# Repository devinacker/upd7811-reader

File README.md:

This is a PCB designed to read the internal mask ROM contents from NEC "µCOM-87AD" microcontrollers (µPD7811 aka uPD7811, etc.) and automatically output them in Intel hex format over serial.

# Specs

- Support for all NEC "µCOM-87AD" series microcontrollers:
  - uPD7811
  - uPD78C11
  - uPD78C12
  - uPD78C14
  - uPD78C18
- Automatic ROM size detection (4/8/16/32kb)
- Power input: 7.5-9V DC, center positive
- Serial output: 115200 baud, 8N1, Intel hex format

# Usage

Zipped gerbers and ROM are available from the releases page.

- Burn the firmware ROM to a 27C256 or compatible EPROM or flash chip (e.g. Atmel AT29C256, Winbond W27E257).
- Assemble the board (all parts are through-hole for convenience).
- Connect the 2-pin serial header to a USB UART adapter or something similar. Configure your computer's serial port as described in "Specs".
- Plug in power and turn the board on. The ROM dump will automatically start being dumped over serial. The "Ready" LED will flash while this is in progress, then becomes solid once it's finished.
- Press Reset or cycle power to dump again, if needed.

The resulting Intel hex file can be converted to a raw ROM image using objcopy, SRecord, or similar tools.

# Parts

| Ref | Part |
| --- | --- |
| C1, C2 | 22pF ceramic |
| C3, C4, C5, C6, C7, C8 | 0.1µF ceramic |
| C9 | 0.22µF electrolytic |
| D1 | generic 5mm 2V LED (power) |
| D2 | generic 5mm 2V LED (status) |
| D3 | 1N4001 |
| J1 | generic 3-pin barrel jack |
| J2 | 1x2 pin header, 2.54mm |
| R1, R2 | 22k ohm, 1/8 watt |
| R3, R4, R5, R6, R7 | 1k ohm, 1/8 watt |
| RN1, RN2, RN5, RN6 | 9-pin 22k ohm SIP resistors |
| RN3, RN4 | 5-pin 22k ohm SIP resistors |
| SW1 | generic 6mm tactile switch (optional, for reset) |
| SW2 | OS102011MS2QN1 |
| U1 | µPD78(C)11/12/14/18, 64-pin QUIP<br/>(four 1x16 2.54mm machined pin sockets recommended)
| U2 | 74HCT373 |
| U3 | 74HCT14 |
| U4 | 27C256 EPROM or compatible |
| U5 | LM7805 |
| Y1 | 11.0592MHz crystal |

# Disclaimer

Use this board at your own risk. It was designed to be simple, but assumes you have basic experience working with electronics, including soldering. I am not responsible if you happen to blow something up.

# License

PCB design and schematics are released under the Creative Commons Attribution-ShareAlike 4.0 (CC BY-SA) license. The firmware source (in the `rom` directory) is released as public domain.

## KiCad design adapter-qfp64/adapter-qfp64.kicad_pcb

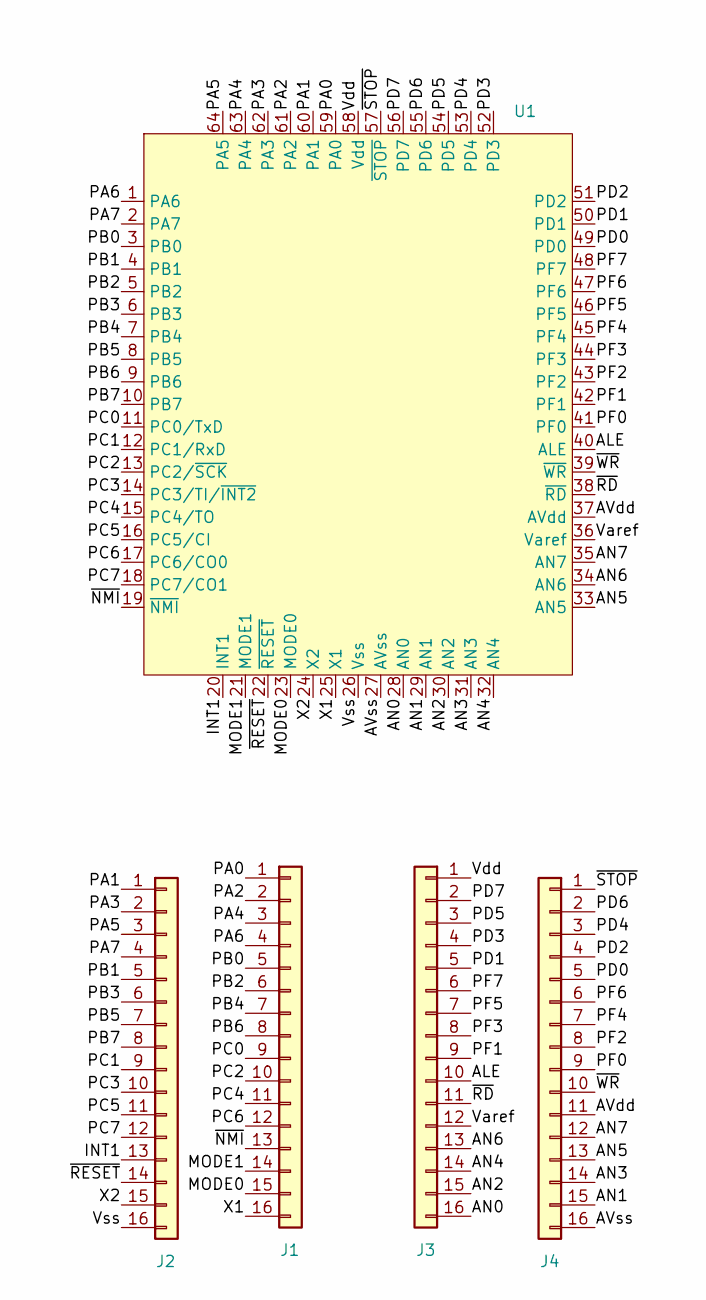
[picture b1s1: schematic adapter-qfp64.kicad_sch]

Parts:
J1, J2, J3, J4: Conn_01x16; PinHeader_1x16_P2.54mm_Vertical
U1: Package_QFP64

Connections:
/ALE: J3.10, U1.40 (ALE)
/AN0: J3.16, U1.28 (AN0)
/AN1: J4.15, U1.29 (AN1)
/AN2: J3.15, U1.30 (AN2)
/AN3: J4.14, U1.31 (AN3)
/AN4: J3.14, U1.32 (AN4)
/AN5: J4.13, U1.33 (AN5)
/AN6: J3.13, U1.34 (AN6)
/AN7: J4.12, U1.35 (AN7)
/AVdd: J4.11, U1.37 (AVdd)
/AVss: J4.16, U1.27 (AVss)
/INT1: J2.13, U1.20 (INT1)
/MODE0: J1.15, U1.23 (MODE0)
/MODE1: J1.14, U1.21 (MODE1)
/PA0: J1.1, U1.59 (PA0)
/PA1: J2.1, U1.60 (PA1)
/PA2: J1.2, U1.61 (PA2)
/PA3: J2.2, U1.62 (PA3)
/PA4: J1.3, U1.63 (PA4)
/PA5: J2.3, U1.64 (PA5)
/PA6: J1.4, U1.1 (PA6)
/PA7: J2.4, U1.2 (PA7)
/PB0: J1.5, U1.3 (PB0)
/PB1: J2.5, U1.4 (PB1)
/PB2: J1.6, U1.5 (PB2)
/PB3: J2.6, U1.6 (PB3)
/PB4: J1.7, U1.7 (PB4)
/PB5: J2.7, U1.8 (PB5)
/PB6: J1.8, U1.9 (PB6)
/PB7: J2.8, U1.10 (PB7)
/PC0: J1.9, U1.11 (PC0/TxD)
/PC1: J2.9, U1.12 (PC1/RxD)
/PC2: J1.10, U1.13 (PC2/~SCK)
/PC3: J2.10, U1.14 (PC3/TI/~INT2)
/PC4: J1.11, U1.15 (PC4/TO)
/PC5: J2.11, U1.16 (PC5/CI)
/PC6: J1.12, U1.17 (PC6/CO0)
/PC7: J2.12, U1.18 (PC7/CO1)
/PD0: J4.5, U1.49 (PD0)
/PD1: J3.5, U1.50 (PD1)
/PD2: J4.4, U1.51 (PD2)
/PD3: J3.4, U1.52 (PD3)
/PD4: J4.3, U1.53 (PD4)
/PD5: J3.3, U1.54 (PD5)
/PD6: J4.2, U1.55 (PD6)
/PD7: J3.2, U1.56 (PD7)
/PF0: J4.9, U1.41 (PF0)
/PF1: J3.9, U1.42 (PF1)
/PF2: J4.8, U1.43 (PF2)
/PF3: J3.8, U1.44 (PF3)
/PF4: J4.7, U1.45 (PF4)
/PF5: J3.7, U1.46 (PF5)
/PF6: J4.6, U1.47 (PF6)
/PF7: J3.6, U1.48 (PF7)
/Varef: J3.12, U1.36 (Varef)
/Vdd: J3.1, U1.58 (Vdd)
/Vss: J2.16, U1.26 (Vss)
/X1: J1.16, U1.25 (X1)
/X2: J2.15, U1.24 (X2)
/~NMI: J1.13, U1.19 (~NMI)
/~RD: J3.11, U1.38 (~RD)
/~RESET: J2.14, U1.22 (~RESET)
/~STOP: J4.1, U1.57 (~STOP)
/~WR: J4.10, U1.39 (~WR)

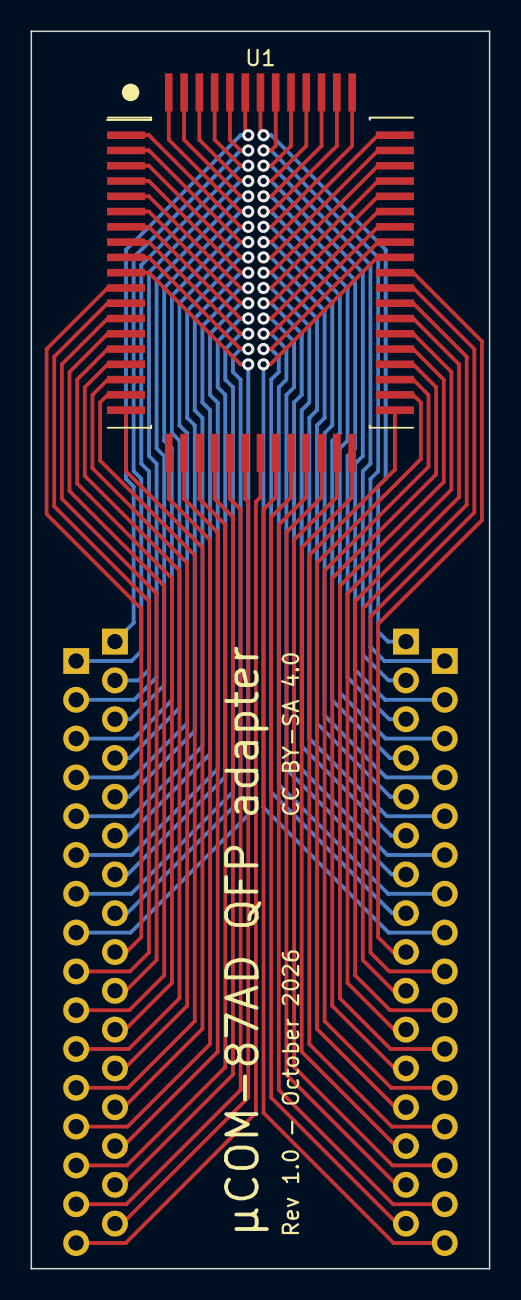
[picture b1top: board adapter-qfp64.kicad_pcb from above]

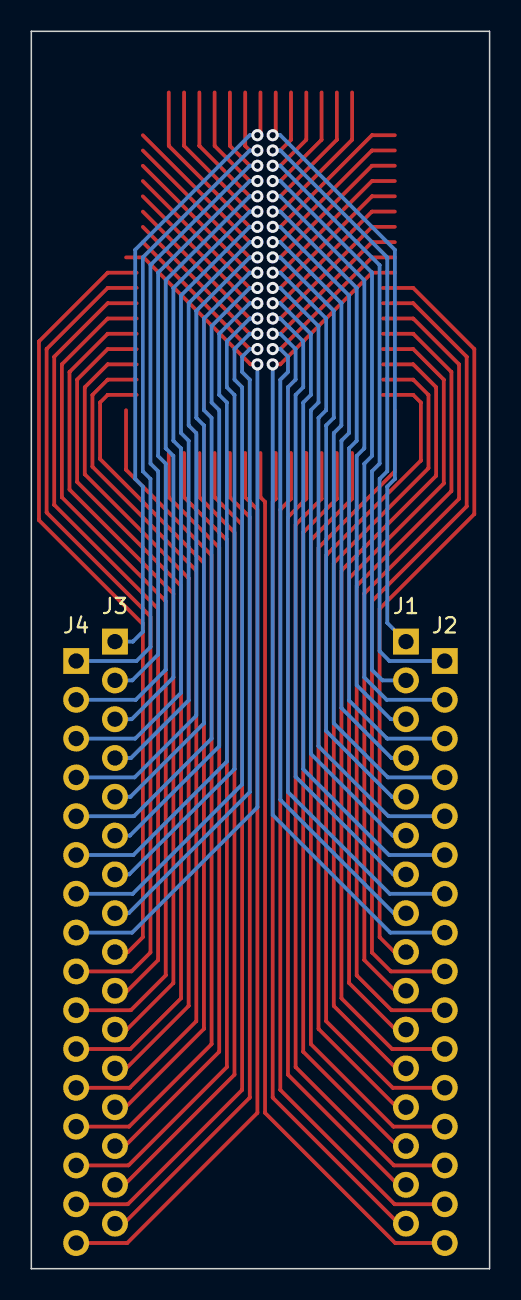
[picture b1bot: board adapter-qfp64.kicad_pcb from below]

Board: 2 copper layers, 30.0 x 81.0 mm, 5 parts (4 on the bottom side), 64 nets.

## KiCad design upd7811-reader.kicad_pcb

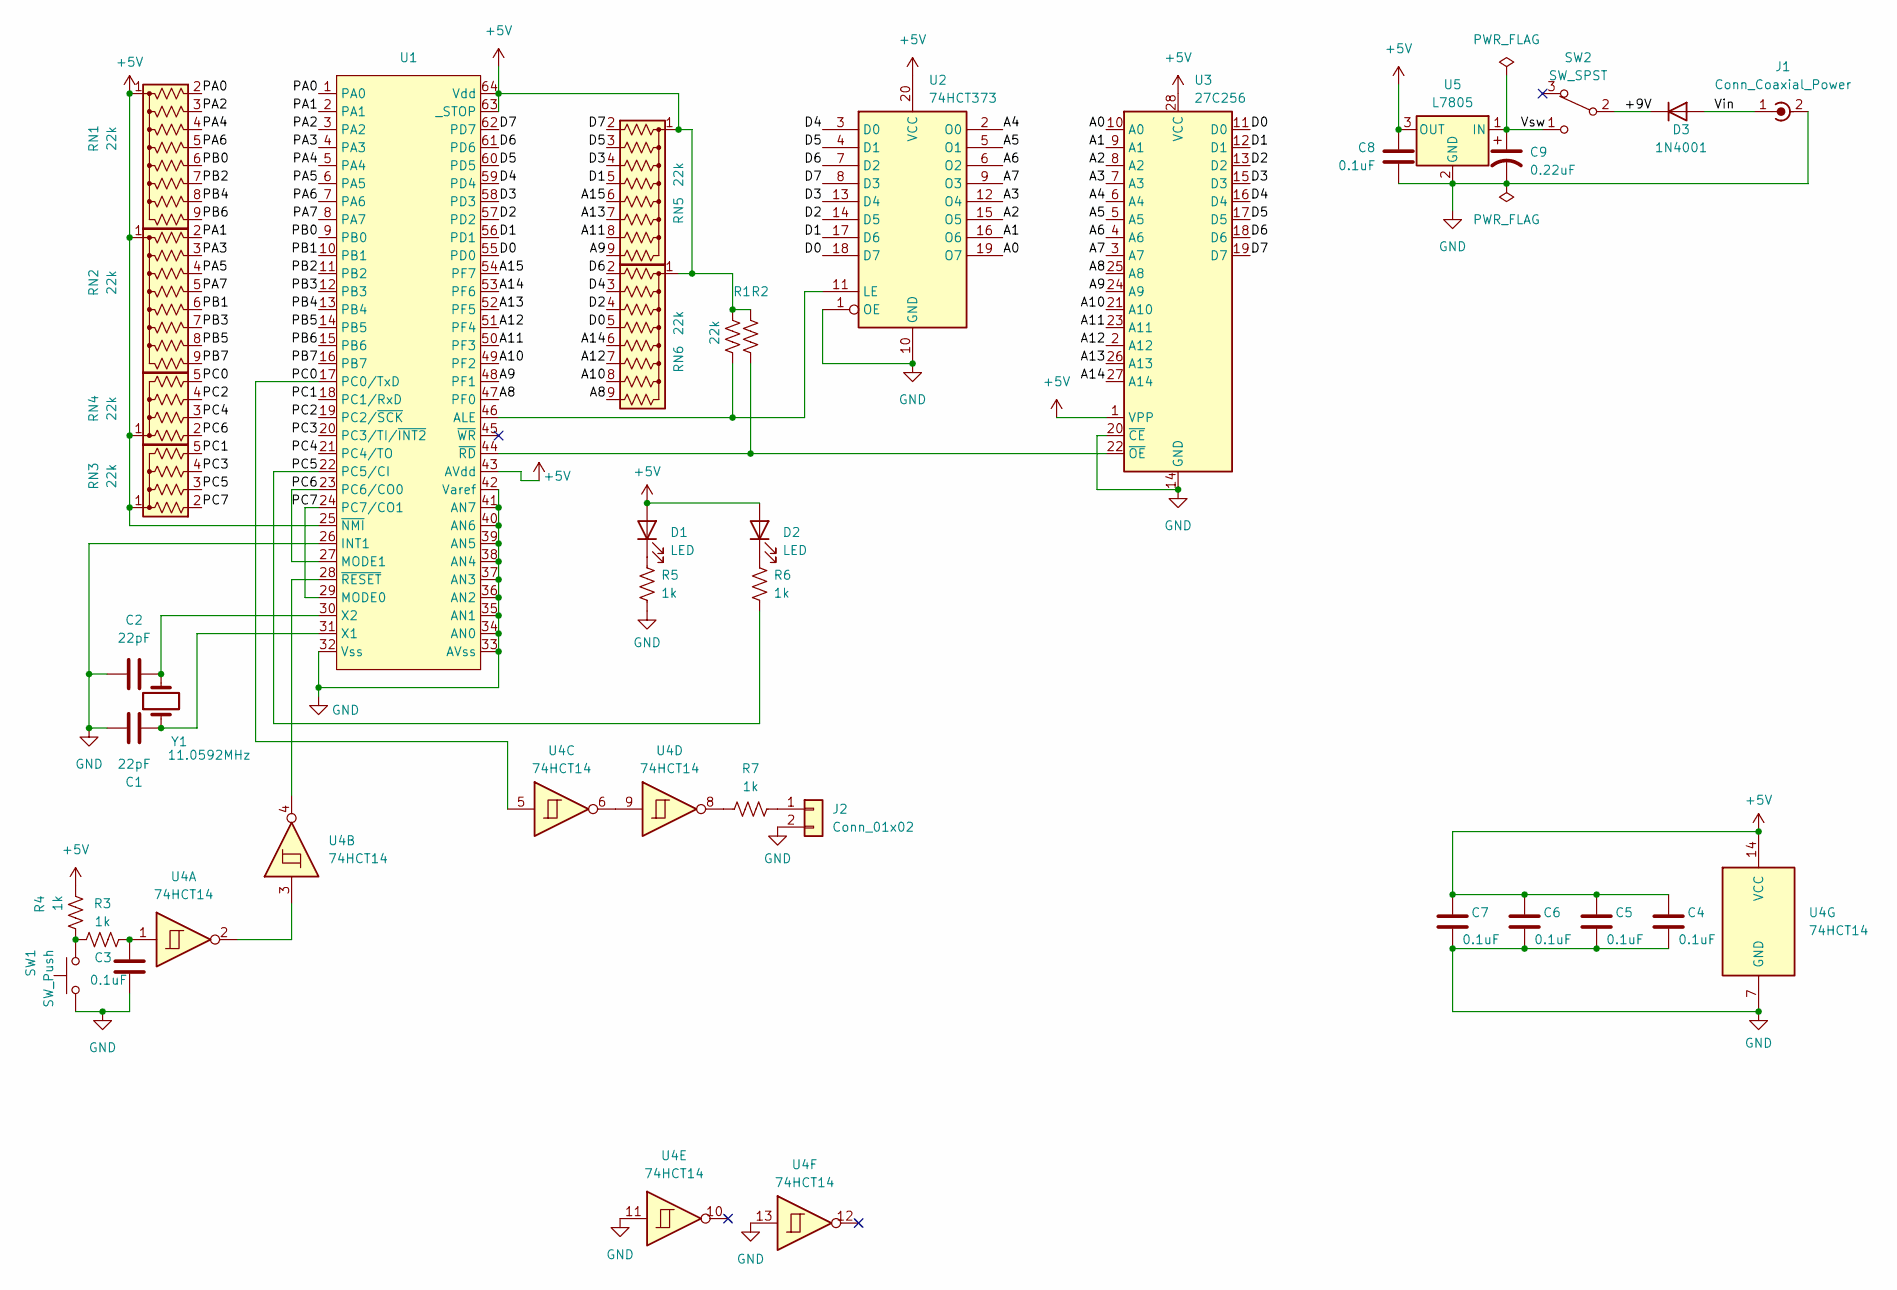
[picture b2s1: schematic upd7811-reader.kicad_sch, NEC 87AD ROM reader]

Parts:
C1, C2: 22pF; C_Disc_D3.8mm_W2.6mm_P2.50mm
C3, C4, C5, C6, C7, C8: 0.1uF; C_Disc_D3.8mm_W2.6mm_P2.50mm
C9: 0.22uF; CP_Radial_D5.0mm_P2.50mm
D1, D2: LED; LED_D5.0mm
D3: 1N4001; D_DO-41_SOD81_P10.16mm_Horizontal
J1: Conn_Coaxial_Power; BarrelJack_Wuerth_6941xx301002
J2: Conn_01x02; PinHeader_1x02_P2.54mm_Vertical
R1, R2: 22k; R_Axial_DIN0204_L3.6mm_D1.6mm_P5.08mm_Horizontal
R3, R4, R5, R6, R7: 1k; R_Axial_DIN0204_L3.6mm_D1.6mm_P5.08mm_Horizontal
RN1, RN2, RN5, RN6: 22k; R_Array_SIP9
RN3, RN4: 22k; R_Array_SIP5
SW1: SW_Push; SW_PUSH_6mm
SW2: SW_SPST; SW_Slide_1P2T_CK_OS102011MS2Q
U1: Package_QUIP64
U2: 74HCT373; DIP-20_W7.62mm
U3: 27C256; DIP-28_W15.24mm
U4: 74HCT14; DIP-14_W7.62mm
U5: L7805; TO-220-3_Horizontal_TabDown
Y1: 11.0592MHz; Crystal_HC49-4H_Vertical

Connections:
+5V: C4.1, C5.1, C6.1, C7.1, C8.1, D1.2 (A), D2.2 (A), R1.1, R2.1, R4.1, RN1.1 (common), RN2.1 (common), RN3.1 (common), RN4.1 (common), RN5.1 (common), RN6.1 (common), U1.25 (~NMI), U1.43 (AVdd), U1.63 (_STOP), U1.64 (Vdd), U2.20 (VCC), U3.1 (VPP), U3.28 (VCC), U4.14 (VCC), U5.3 (OUT)
/+9V: D3.1 (K), SW2.2 (B)
/A0: U2.19 (O7), U3.10 (A0)
/A1: U2.16 (O6), U3.9 (A1)
/A2: U2.15 (O5), U3.8 (A2)
/A3: U2.12 (O4), U3.7 (A3)
/A4: U2.2 (O0), U3.6 (A4)
/A5: U2.5 (O1), U3.5 (A5)
/A6: U2.6 (O2), U3.4 (A6)
/A7: U2.9 (O3), U3.3 (A7)
/A8: RN6.9 (R8), U1.47 (PF0), U3.25 (A8)
/A9: RN5.9 (R8), U1.48 (PF1), U3.24 (A9)
/A10: RN6.8 (R7), U1.49 (PF2), U3.21 (A10)
/A11: RN5.8 (R7), U1.50 (PF3), U3.23 (A11)
/A12: RN6.7 (R6), U1.51 (PF4), U3.2 (A12)
/A13: RN5.7 (R6), U1.52 (PF5), U3.26 (A13)
/A14: RN6.6 (R5), U1.53 (PF6), U3.27 (A14)
/A15: RN5.6 (R5), U1.54 (PF7)
/D0: RN6.5 (R4), U1.55 (PD0), U2.18 (D7), U3.11 (D0)
/D1: RN5.5 (R4), U1.56 (PD1), U2.17 (D6), U3.12 (D1)
/D2: RN6.4 (R3), U1.57 (PD2), U2.14 (D5), U3.13 (D2)
/D3: RN5.4 (R3), U1.58 (PD3), U2.13 (D4), U3.15 (D3)
/D4: RN6.3 (R2), U1.59 (PD4), U2.3 (D0), U3.16 (D4)
/D5: RN5.3 (R2), U1.60 (PD5), U2.4 (D1), U3.17 (D5)
/D6: RN6.2 (R1), U1.61 (PD6), U2.7 (D2), U3.18 (D6)
/D7: RN5.2 (R1), U1.62 (PD7), U2.8 (D3), U3.19 (D7)
/PA0: RN1.2 (R1), U1.1 (PA0)
/PA1: RN2.2 (R1), U1.2 (PA1)
/PA2: RN1.3 (R2), U1.3 (PA2)
/PA3: RN2.3 (R2), U1.4 (PA3)
/PA4: RN1.4 (R3), U1.5 (PA4)
/PA5: RN2.4 (R3), U1.6 (PA5)
/PA6: RN1.5 (R4), U1.7 (PA6)
/PA7: RN2.5 (R4), U1.8 (PA7)
/PB0: RN1.6 (R5), U1.9 (PB0)
/PB1: RN2.6 (R5), U1.10 (PB1)
/PB2: RN1.7 (R6), U1.11 (PB2)
/PB3: RN2.7 (R6), U1.12 (PB3)
/PB4: RN1.8 (R7), U1.13 (PB4)
/PB5: RN2.8 (R7), U1.14 (PB5)
/PB6: RN1.9 (R8), U1.15 (PB6)
/PB7: RN2.9 (R8), U1.16 (PB7)
/PC0: RN4.5 (R4), U1.17 (PC0/TxD), U4.5
/PC1: RN3.5 (R4), U1.18 (PC1/RxD)
/PC2: RN4.4 (R3), U1.19 (PC2/~SCK)
/PC3: RN3.4 (R3), U1.20 (PC3/TI/~INT2)
/PC4: RN4.3 (R2), U1.21 (PC4/TO)
/PC5: R6.2, RN3.3 (R2), U1.22 (PC5/CI)
/PC6: RN4.2 (R1), U1.23 (PC6/CO0), U1.27 (MODE1)
/PC7: RN3.2 (R1), U1.24 (PC7/CO1), U1.29 (MODE0)
/Vin: D3.2 (A), J1.1 (In)
/Vsw: C9.1, SW2.1 (C), U5.1 (IN)
GND: C1.1, C2.1, C3.2, C4.2, C5.2, C6.2, C7.2, C8.2, C9.2, J1.2 (Ext), J2.2, R5.2, SW1.1, U1.26 (INT1), U1.32 (Vss), U1.33 (AVss), U1.34 (AN0), U1.35 (AN1), U1.36 (AN2), U1.37 (AN3), U1.38 (AN4), U1.39 (AN5), U1.40 (AN6), U1.41 (AN7), U1.42 (Varef), U2.1 (OE), U2.10 (GND), U3.14 (GND), U3.20 (~CE), U4.7 (GND), U4.11, U4.13, U5.2 (GND)
unnamed: C3.1, R3.2, U4.1
unnamed: D1.1 (K), R5.1
unnamed: D2.1 (K), R6.1
unnamed: J2.1, R7.2
unnamed: R3.1, R4.2, SW1.2
unnamed: R7.1, U4.8
unnamed: R1.2, U1.46 (ALE), U2.11 (LE)
unnamed: C1.2, U1.31 (X1), Y1.1
unnamed: C2.2, U1.30 (X2), Y1.2
unnamed: R2.2, U1.44 (~RD), U3.22 (~OE)
unnamed: U1.28 (~RESET), U4.4
unnamed: U4.2, U4.3
unnamed: U4.6, U4.9

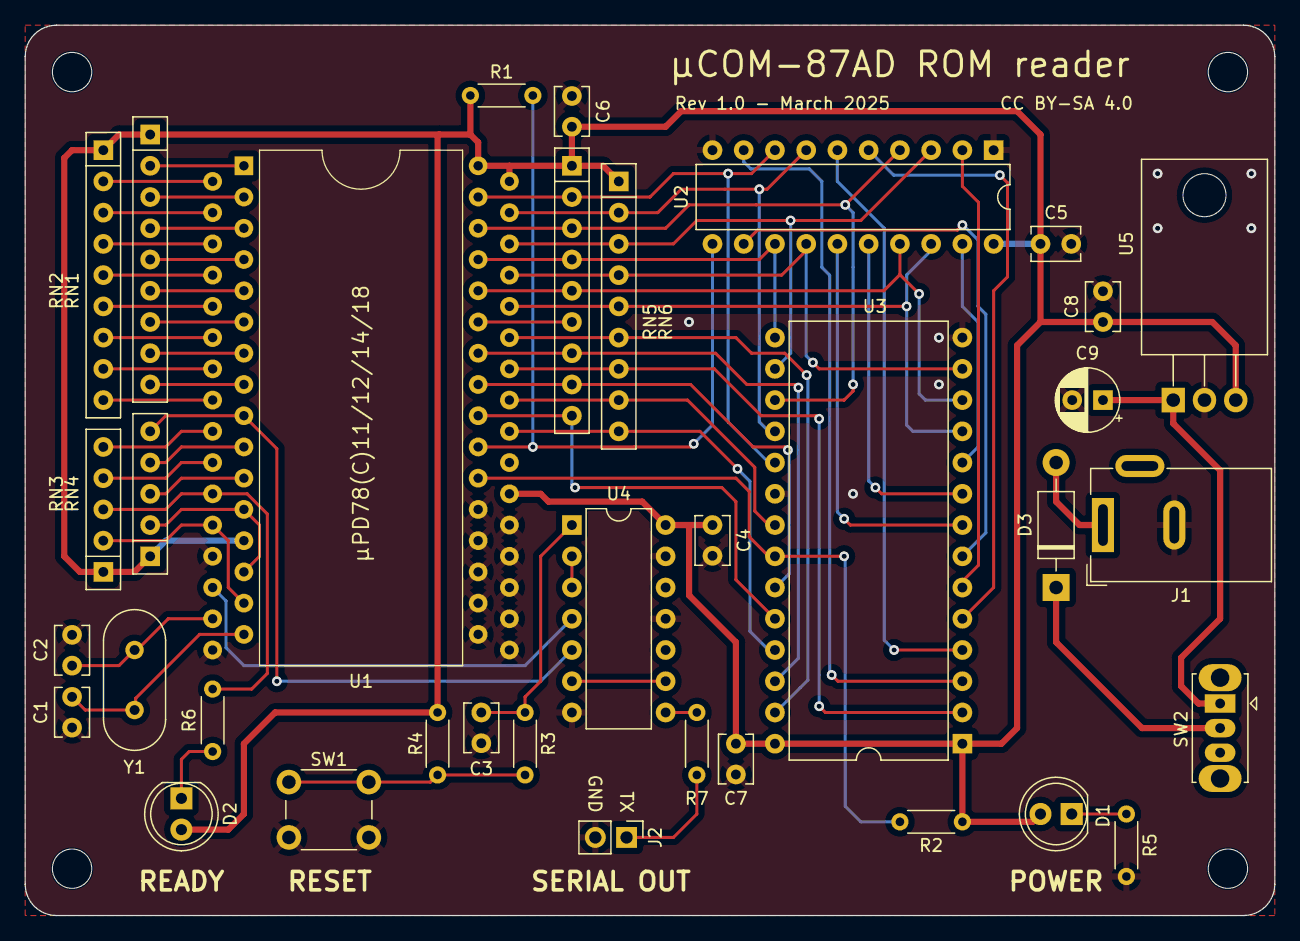
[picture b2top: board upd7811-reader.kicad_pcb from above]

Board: 2 copper layers, 101.6 x 72.4 mm, 35 parts (0 on the bottom side), 66 nets.

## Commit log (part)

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2025-02-10 init
2025-03-02 initial commit for ROM
2025-03-02 bump up serial to 115200 baud
2025-03-08 the rest of everything

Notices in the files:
adapter-qfp64/adapter-qfp64.kicad_pcb:
CC BY-SA 4.0
